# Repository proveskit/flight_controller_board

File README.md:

# flight_controller_board
This is the repo for the main Flight Controller (FC) Board for the PROVES Kit.

For detailed documentation on the Flight Controller Board, check out the docs [here](https://docs.proveskit.space/en/latest/core_documentation/hardware/FC_board/). 

# Quick Start
If you have just received a flight controller board, getting started with developing on one is quick and easy! V4 Flight Controller Boards require the soldering of the JP1 solder jumper to enable powering via USB (it is in the bottom right). V5 Flight Controller Boards have a nifty switch! Once the board is powered up you can refer to [our quick start guide](https://proveskit.github.io/pysquared/getting-started/) for notes on how to get code loaded and the board running.

## Flight Heritage and Version History
| Version | Flights | Status |
| ----------- | ----------- | ----------- |
| V0 | Unflown | Deprecated |
| V1 | Pleiades - Yearling, Pleiades - Squared | Deprecated |
| V2 | Unflown | Deprecated |
| V3 | Unflown | Deprecated |
| V4a (aka V1a Internal) | Unflown | Deprecated |
| V4b | Unflown | Deprecated |
| V4c | Pleiades - Orpheus, InspireFly Content Cube | Dev Only Support |
| V5dev | Unflown | Deprecated |
| V5a | Unflown | Deprecated |
| V5b | Unflown | Deprecated |
| V5c | Unflown | Deprecated |
| V5d | Unflown | Deprecated |
| V5d Pro | Unflown | Supported |
| V5d Pro Rev 1 | PROVES - Alycone, PROVES - Atlas, PROVES - Electra, HUCSat-1 | Supported |
| V5d Pro Rev 2 | Unflown | Supported |
| V5e | Unflown | Dev Support Only |
| V5e Pro Rev 1 | PROVES - Maia, PROVES - Taygeta | Supported |

V0 through V3 Flight Controller Boards were the cornerstone of the 2023 Release V1 PROVES Kit. With the 2024 V2 PROVES Kit we introduced the V4 Flight Controller board and changed the version scheme to have `a`, `b`, `c`, etc varients of a single version rather than ascending the version ladder in record time (we'd be on V17 now if we did that!). This change was primarily based on the idea that a revisions on a major version number would be similar enough to each other to not require completely different firmware to be compiled for operation.

For V5d we added a "Pro" for "Production" version!

## Current Features
The Latest (V5e) FC board implements the following components: 
- RP2350A Microcontroller
- 128M-Bit W25Q128JVSIQ Flash Memory
- HopeRF RFM9X UHF Radio Module Slot
- Ebyte E28-2G4M27S S-Band Radio
- OreSat Derived Radiation Tolerant Watchdog Circuit!
- SD Card Emulating NAND Flash
- TCA9548ARGER(Q1) I2C Multiplexer
- RV3028 Real Time Clock
- LSM6DSOTR Accelerometer and Gyroscope
- LSM303AGRTR Magnetometer
- MCP23017T-E/SS I2C GPIO Expander
- AP22652W6-7 Load Switches
- MCP9808T-E/MS I2C Temperature Sensor
- LT3652IMSE MPP Solar Charge Controller
- INA260 I2C Power Monitor
- TPS54225PWPR 3.3V Switching Voltage Regulator
- TPS54225PWPR 5V Switching Voltage Regulator

## Current Status and Upcoming Plans
The latest V5 generation of Flight Controller boards takes in lessons learned from Orpheus and InspireFly to create a 2025 Release V3 of the PROVES Kit. Both V5dev and V5a will not be distributed beyond the PROVES developer community due to significant design errata that make them tricky to work with. The incoming V5b is intended to be the stable release for this version of the kit.

Lessons learned from V3 PROVES Kit will be directly applied to the creation of a V6 Flight Controller Board generation for V4 PROVES Kit. We plan to continually support the latest and previous PROVES Kit Versions starting with the V3 Release. This means that V2 Kits will continue to receive updates until V4 is officially released.

### The Plan From 2024
Currently we are in production for V1.5 PROVES Kits, which are an interesting middle step between the V1 Kits (which flew on all the Yearling satellites) and V2 (which we are hoping to fly on all the Pleiades Five satellites). One of the main changes between V1 and V2 will be transitioning the flight controller from being mounted to the Z+ face of the satellite to an internal board. This move is intended to improve the thermal performance and radiation tolerance of the avionics stack. 

## Legacy Support
As of May 2025 we are officially no longer supporting any FC boards prior to V4. If you happen to have a PROVES Kit (usually a V1 PROVES Kit manufactured in 2023) that still uses a V1, V2, or V3 Flight Controller board and need support, please open an issue on this GitHub repo and ping @mikefly123 for help! 

### (LEGACY) Internal FC Boards 
1. If you do not plan on connecting a battery board, ensure that the ```JP1``` solder jumper is connected to enable powering the board via USB.
2. Solder on the Radio Module and an antenna or SMA connect as needed.
3. Plug in a USB Cable!
4. If a CircuitPython file system does not appear, you may have to flash the board with firmware. This firmware can be found [here](https://github.com/proveskit/flight_controller_board/tree/main/Firmware)
5. Continue to the [PROVES Quick Start Guide](https://docs.proveskit.space/en/latest/quick_start/proves_quick_start/) for more!
> Note: If you are using USB power for the radio it may not perform as expected due to a lack of 5V power. 

> NOTE: The V1 and V2 boards are not recommended for flight due to a high suspectibility to thermal and radiation effects. These boards are still perfectly fine for ground testing and educational use. Bronco Space is currently conducting testing to flush out these issues and will be mitigating these potential issues in V3. If you would like to receive eval hardware of the new version please contact Michael Pham: mlpham@cpp.edu

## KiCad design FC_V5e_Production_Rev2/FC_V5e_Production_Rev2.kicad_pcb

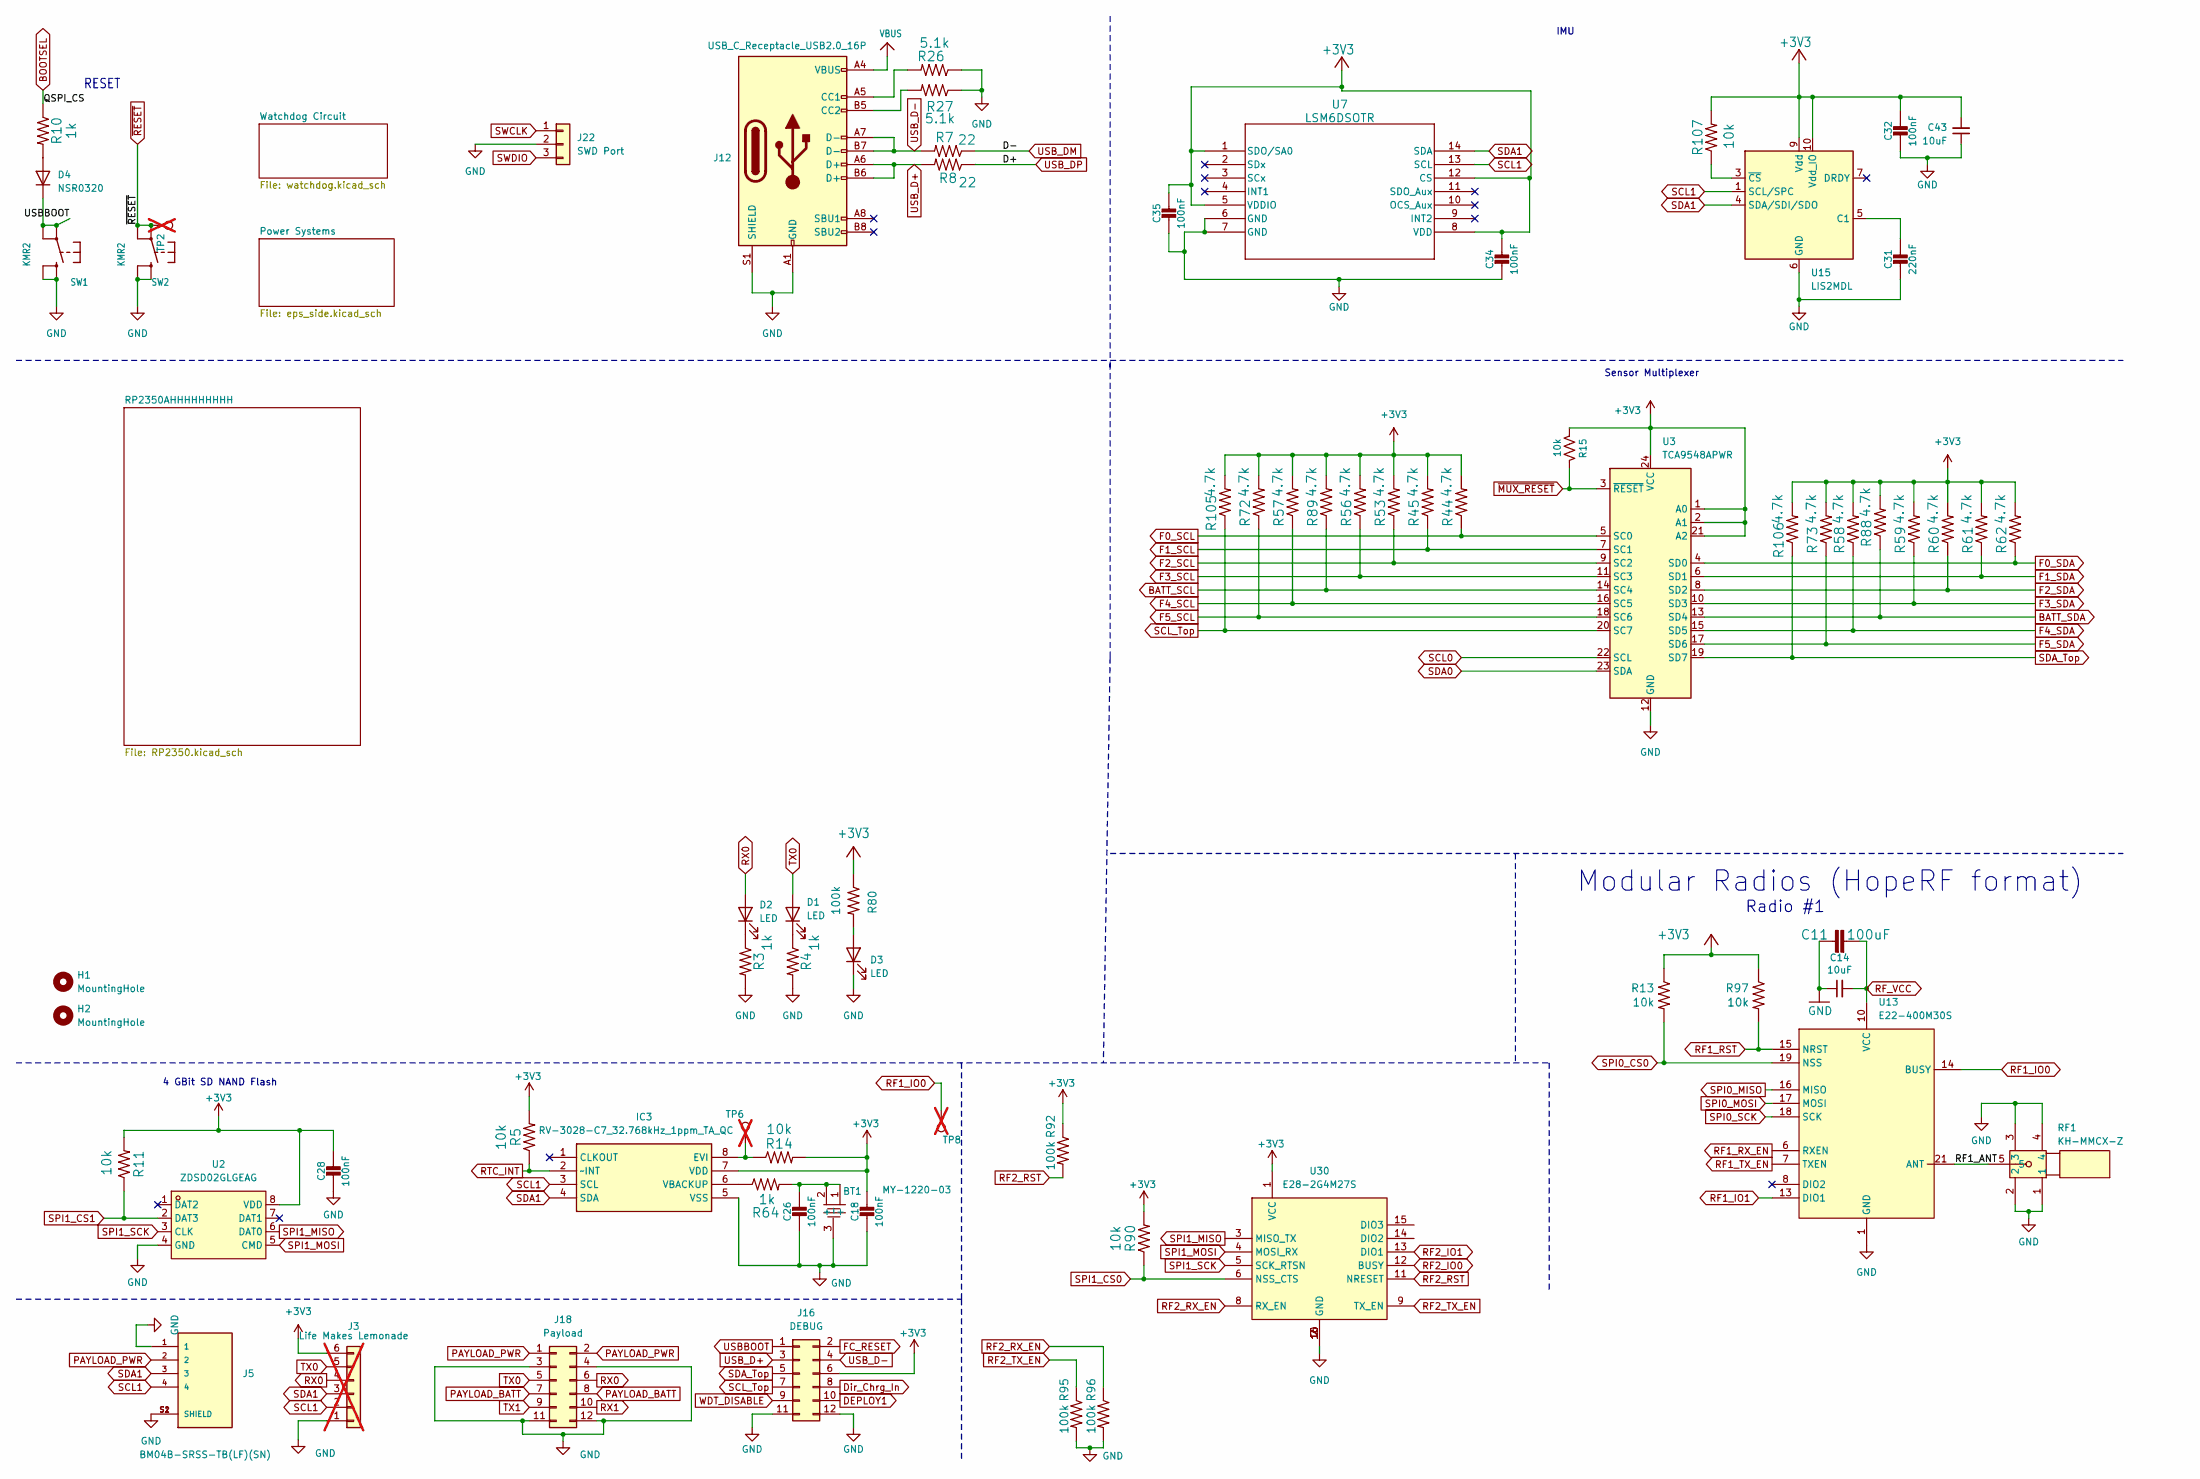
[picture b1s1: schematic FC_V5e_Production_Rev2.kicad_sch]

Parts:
BT1: MY-1220-03; BAT-SMD_MY-1220-03; LCSC Part C964818
C11: 100uF; C_1210_3225Metric
C14: 10uF; C_0603_1608Metric
C18, C26, C28, C32, C34, C35: 100nF; C_0402_1005Metric
C31: 220nF; C_0402_1005Metric
C43: 10uF; C_0603_1608Metric; MPN GRT188R61C106KE13D
D1, D2, D3: LED; LED_0603_1608Metric
D4: NSR0320; D_SOD-323F
H1, H2: MountingHole
IC3: RV-3028-C7_32.768kHz_1ppm_TA_QC; RV3028C7; Mouser Part Number 428-203591-MG01
J3: Life Makes Lemonade; PinHeader_1x06_P2.54mm_Vertical; not fitted
J5: BM04B-SRSS-TB(LF)(SN); JST_BM04B-SRSS-TB(LF)(SN); MPN BM04B-SRSS-TB(LF)(SN)
J12: USB_C_Receptacle_USB2.0_16P; USB_C_Receptacle_HRO_TYPE-C-31-M-12; MPN TYPE-C-31-M-12
J16: DEBUG; Hirose_DF11-12DP-2DSA_2x06_P2.00mm_Vertical; MPN DF11-12DP-2DSA(08)
J18: Payload; Hirose_DF11-12DP-2DSA_2x06_P2.00mm_Vertical; MPN DF11-12DP-2DSA(08)
J22: SWD Port; JST_SH_BM03B-SRSS-TB_1x03-1MP_P1.00mm_Vertical; MPN BM03B-SRSS-TB(LF)(SN)
R3, R4, R10, R64: 1k; R_0603_1608Metric
R5, R11, R13, R14, R15, R90, R97, R107: 10k; R_0603_1608Metric
R7, R8: 22; R_0402_1005Metric
R26, R27: 5.1k; R_0603_1608Metric
R44, R45, R53, R56, R57, R58, R59, R60, R61, R62, R72, R73, R88, R89, R105, R106: 4.7k; R_0402_1005Metric
R80, R92, R95, R96: 100k; R_0603_1608Metric
RF1: KH-MMCX-Z; MMCX-TH_KH-MMCX-Z; LCSC Part C530664
SW1, SW2: KMR2; BTN_KMR2_4.6X2.8
TP2, TP6, TP8: RESET; TestPoint_Loop_D1.80mm_Drill1.0mm_Beaded; not fitted
U2: ZDSD02GLGEAG; LGA-8_L8.0-W6.0-P1.27-TL-1; LCSC Part C2875853
U3: TCA9548APWR; TSSOP-24_4.4x7.8mm_P0.65mm
U7: LSM6DSOTR; LGA-14_3x2.5mm_P0.5mm_LayoutBorder3x4y
U13: E22-400M30S; WIRELM-SMD_E22-400M30S; LCSC Part C411292
U15: LIS2MDL; LGA-12_2x2mm_P0.5mm
U30: E28-2G4M27S; WIRELM-SMD_E28-2G4M2XS; LCSC Part C411312

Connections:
+3V3: C18.1, C28.1, C32.1, C34.1, C35.1, C43.2, IC3.7 (VDD), J3.6, J16.6, R5.2, R11.2, R13.1, R14.2, R15.1, R44.2, R45.2, R53.2, R56.2, R57.2, R58.2, R59.2, R60.2, R61.2, R62.2, R72.2, R73.2, R80.1, R88.2, R89.2, R90.2, R92.1, R97.1, R105.2, R106.2, R107.2, U2.8 (VDD), U3.1 (A0), U3.2 (A1), U3.21 (A2), U3.24 (VCC), U7.1 (SDO/SA0), U7.5 (VDDIO), U7.8 (VDD), U7.12 (CS), U15.9 (Vdd), U15.10 (Vdd_IO), U30.1 (VCC); also elsewhere on the board
/RF1_ANT: RF1.5, U13.21 (ANT)
BATT_SCL: R89.1, U3.14 (SC4); also elsewhere on the board
BATT_SDA: R88.1, U3.13 (SD4); also elsewhere on the board
BOOTSEL: R10.1; also elsewhere on the board
DEPLOY1: J16.10; also elsewhere on the board
Dir_Chrg_In: J16.8; also elsewhere on the board
F0_SCL: R44.1, U3.5 (SC0); also elsewhere on the board
F0_SDA: R62.1, U3.4 (SD0); also elsewhere on the board
F1_SCL: R45.1, U3.7 (SC1); also elsewhere on the board
F1_SDA: R61.1, U3.6 (SD1); also elsewhere on the board
F2_SCL: R53.1, U3.9 (SC2); also elsewhere on the board
F2_SDA: R60.1, U3.8 (SD2); also elsewhere on the board
F3_SCL: R56.1, U3.11 (SC3); also elsewhere on the board
F3_SDA: R59.1, U3.10 (SD3); also elsewhere on the board
F4_SCL: R57.1, U3.16 (SC5); also elsewhere on the board
F4_SDA: R58.1, U3.15 (SD5); also elsewhere on the board
F5_SCL: R72.1, U3.18 (SC6); also elsewhere on the board
F5_SDA: R73.1, U3.17 (SD6); also elsewhere on the board
FC_RESET: J16.2, SW2.A, SW2.A' (P1), TP2.1 (1_1); also elsewhere on the board
GND: BT1.3 (-), C11.1, C14.1, C18.2, C26.2, C28.2, C31.2, C32.2, C34.2, C35.2, C43.1, D3.1 (K), IC3.5 (VSS), J3.1, J5.1, J5.S1 (SHIELD), J5.S2 (SHIELD), J12.A1 (GND), J12.A12 (GND), J12.B1 (GND), J12.B12 (GND), J12.S1 (SHIELD), J16.11, J16.12, J18.3, J18.4, J18.11, J18.12, J22.2, R3.2, R4.2, R26.1, R27.1, R95.2, R96.2, RF1.1, RF1.2, RF1.3, RF1.4, SW1.B (S), SW1.B' (S1), SW2.B (S), SW2.B' (S1), U2.4 (GND), U3.12 (GND), U7.6 (GND), U7.7 (GND), U13.1 (GND), U13.2 (GND), U13.3 (GND), U13.4 (GND), U13.5 (GND), U13.11 (GND), U13.12 (GND), U13.20 (GND), U13.22 (GND), U15.6 (GND), U15.8 (GND), U30.2 (GND), U30.7 (GND), U30.10 (GND), U30.16 (GND); also elsewhere on the board
unnamed: BT1.1 (+), BT1.2 (+), C26.1, R64.2
unnamed: D1.1 (K), R4.1
unnamed: D2.1 (K), R3.1
unnamed: D3.2 (A), R80.2
unnamed: D4.2 (A), R10.2
unnamed: IC3.8 (EVI), R14.1, TP6.1 (1_1)
unnamed: IC3.6 (VBACKUP), R64.1
unnamed: J12.A5 (CC1), R26.2
unnamed: J12.B5 (CC2), R27.2
unnamed: C31.1, U15.5 (C1)
unnamed: R107.1, U15.3 (~CS)
PAYLOAD_BATT: J18.7, J18.8; also elsewhere on the board
PAYLOAD_PWR: J5.2, J18.1, J18.2; also elsewhere on the board
RF1_IO0: TP8.1 (1_1), U13.14 (BUSY); also elsewhere on the board
RF1_IO1: U13.13 (DIO1); also elsewhere on the board
RF1_RST: R97.2, U13.15 (NRST); also elsewhere on the board
RF1_RX_EN: U13.6 (RXEN); also elsewhere on the board
RF1_TX_EN: U13.7 (TXEN); also elsewhere on the board
RF2_IO0: U30.12 (BUSY); also elsewhere on the board
RF2_IO1: U30.13 (DIO1); also elsewhere on the board
RF2_RST: R92.2, U30.11 (NRESET); also elsewhere on the board
RF2_RX_EN: R96.1, U30.8 (RX_EN); also elsewhere on the board
RF2_TX_EN: R95.1, U30.9 (TX_EN); also elsewhere on the board
RF_VCC: C11.2, C14.2, U13.9 (VCC), U13.10 (VCC); also elsewhere on the board
RTC_INT: IC3.2 (~INT), R5.1; also elsewhere on the board
RX0: D2.2 (A), J3.4, J18.6; also elsewhere on the board
RX1: J18.10; also elsewhere on the board
SCL0: U3.22 (SCL); also elsewhere on the board
SCL1: IC3.3 (SCL), J3.2, J5.4, U7.13 (SCL), U15.1 (SCL/SPC); also elsewhere on the board
SCL_Top: J16.7, R105.1, U3.20 (SC7)
SDA0: U3.23 (SDA); also elsewhere on the board
SDA1: IC3.4 (SDA), J3.3, J5.3, U7.14 (SDA), U15.4 (SDA/SDI/SDO); also elsewhere on the board
SDA_Top: J16.5, R106.1, U3.19 (SD7)
SPI0_CS0: R13.2, U13.19 (NSS); also elsewhere on the board
SPI0_MISO: U13.16 (MISO); also elsewhere on the board
SPI0_MOSI: U13.17 (MOSI); also elsewhere on the board
SPI0_SCK: U13.18 (SCK); also elsewhere on the board
SPI1_CS0: R90.1, U30.6 (NSS_CTS); also elsewhere on the board
SPI1_CS1: R11.1, U2.2 (DAT3); also elsewhere on the board
SPI1_MISO: U2.6 (DAT0), U30.3 (MISO_TX); also elsewhere on the board
SPI1_MOSI: U2.5 (CMD), U30.4 (MOSI_RX); also elsewhere on the board
SPI1_SCK: U2.3 (CLK), U30.5 (SCK_RTSN); also elsewhere on the board
SWCLK: J22.1; also elsewhere on the board
SWDIO: J22.3; also elsewhere on the board
TX0: D1.2 (A), J3.5, J18.5; also elsewhere on the board
TX1: J18.9; also elsewhere on the board
USBBOOT: D4.1 (K), J16.1, SW1.A, SW1.A' (P1)
USB_D+: J12.A6 (D+), J12.B6 (D+), J16.3, R8.2
USB_D-: J12.A7 (D-), J12.B7 (D-), J16.4, R7.2
USB_DM: R7.1; also elsewhere on the board
USB_DP: R8.1; also elsewhere on the board
VBUS: J12.A4 (VBUS), J12.A9 (VBUS), J12.B4 (VBUS), J12.B9 (VBUS); also elsewhere on the board
WDT_DISABLE: J16.9; also elsewhere on the board
~MUX_RESET: R15.2, U3.3 (~RESET); also elsewhere on the board

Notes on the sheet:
4 GBit SD NAND Flash
Radio #1
Modular Radios (HopeRF format)
Sensor Multiplexer
RESET
IMU

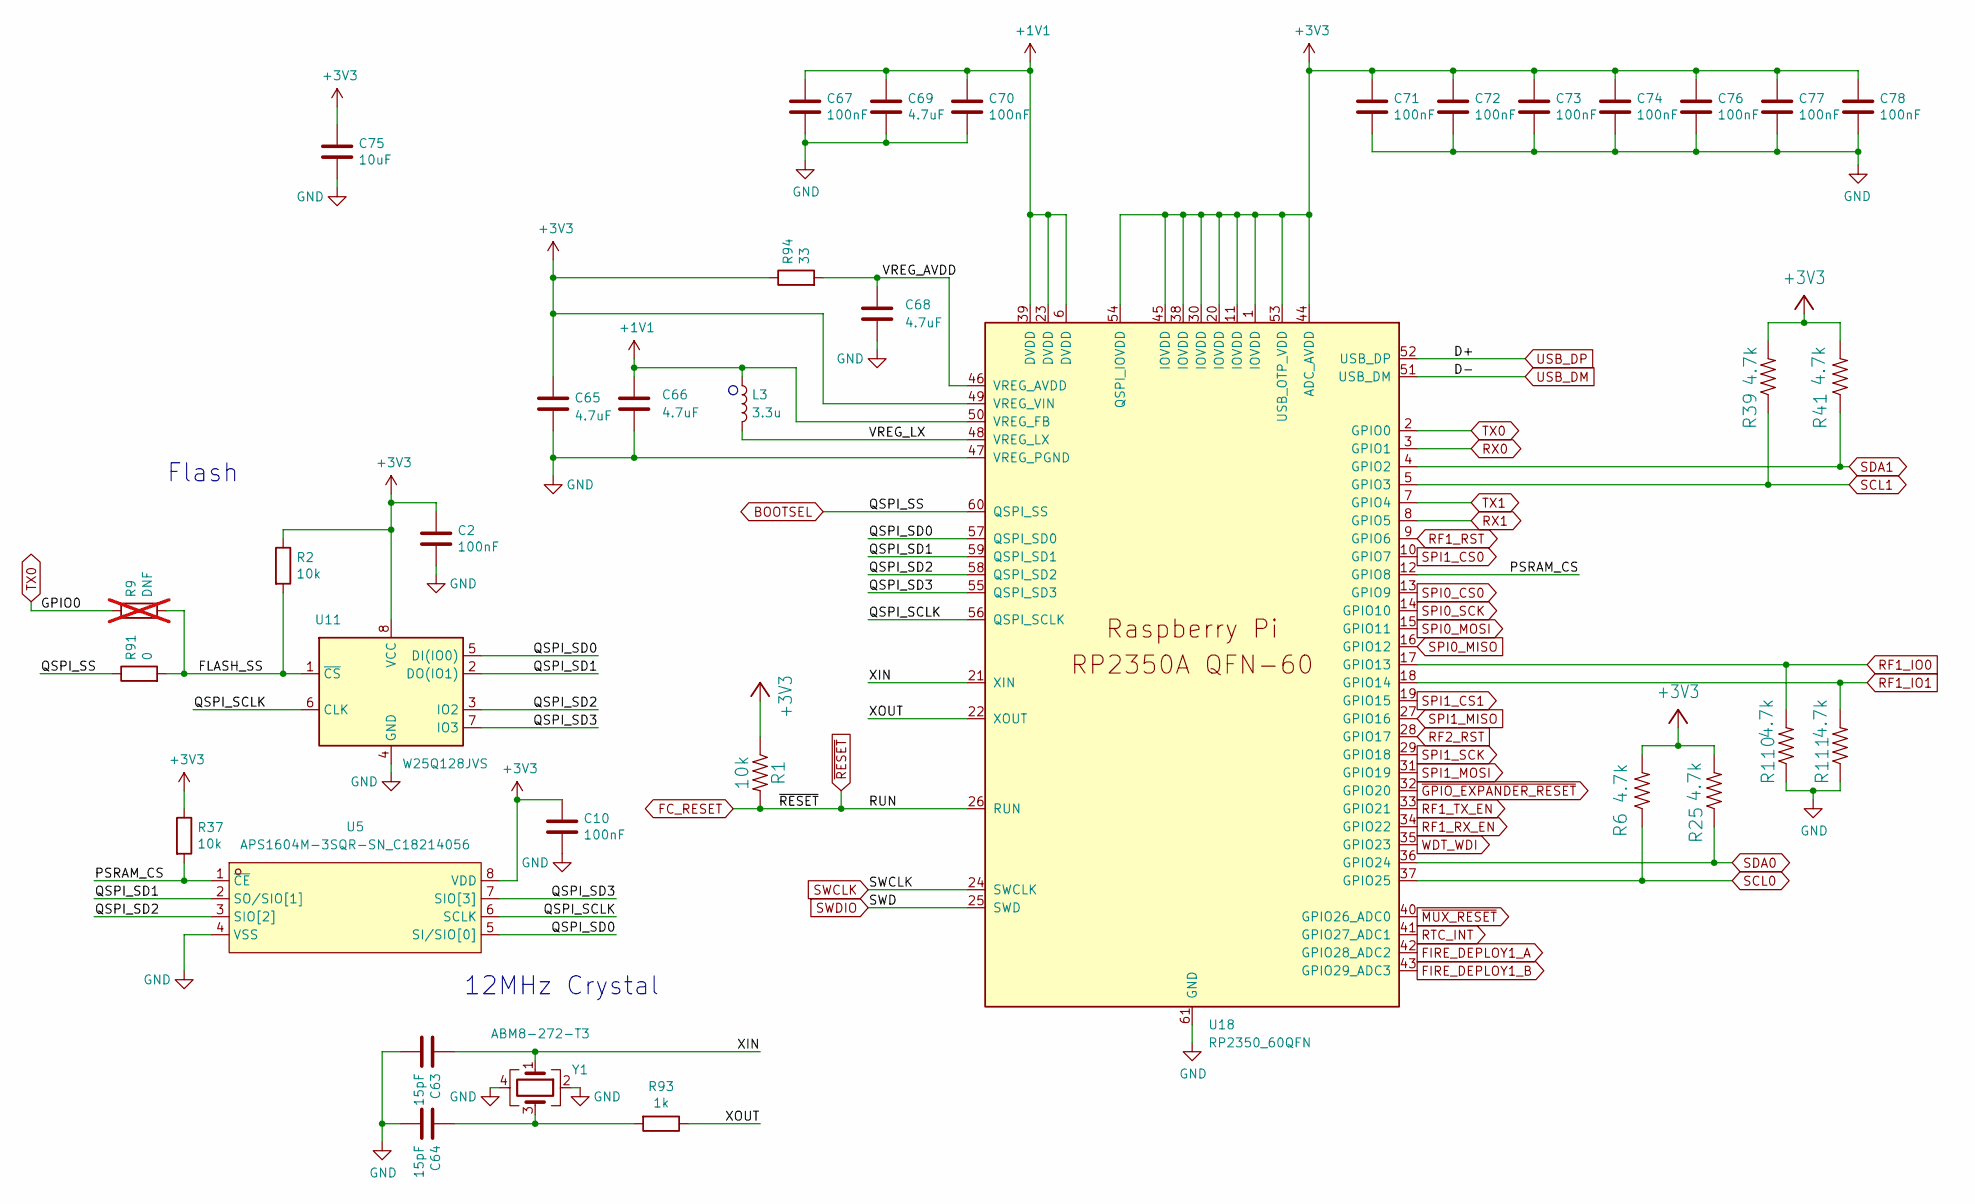
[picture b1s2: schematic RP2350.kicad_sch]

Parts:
C2, C10, C67, C70, C71, C72, C73, C74, C76, C77, C78: 100nF; C_0402_1005Metric
C63, C64: 15pF; C_0402_1005Metric
C65, C66: 4.7uF; C_0402_1005Metric_small_pads
C68, C69: 4.7uF; C_0402_1005Metric
C75: 10uF; C_0805_2012Metric
L3: 3.3u; L_pol_2016
R1: 10k; R_0603_1608Metric
R2, R37: 10k; R_0402_1005Metric
R6, R25, R39, R41, R110, R111: 4.7k; R_0402_1005Metric
R9: DNF; R_0402_1005Metric; not fitted
R91: 0; R_0402_1005Metric
R93: 1k; R_0402_1005Metric
R94: 33; R_0402_1005Metric
U5: APS1604M-3SQR-SN_C18214056; SOIC-8_L4.9-W3.9-P1.27-LS6.0-BL; LCSC Part C18214056
U11: W25Q128JVS; SOIC-8_5.3x5.3mm_P1.27mm
U18: RP2350_60QFN; RP2350-QFN-60-1EP_7x7_P0.4mm_EP3.4x3.4mm_ThermalVias
Y1: ABM8-272-T3; Crystal_SMD_3225-4Pin_3.2x2.5mm

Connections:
+1V1: C66.1, C67.1, C69.1, C70.1, L3.1, U18.6 (DVDD), U18.23 (DVDD), U18.39 (DVDD), U18.50 (VREG_FB)
+3V3: C2.1, C10.1, C65.1, C71.1, C72.1, C73.1, C74.1, C75.1, C76.1, C77.1, C78.1, R1.1, R2.1, R6.2, R25.2, R37.1, R39.2, R41.2, R94.1, U5.8 (VDD), U11.8 (VCC), U18.1 (IOVDD), U18.11 (IOVDD), U18.20 (IOVDD), U18.30 (IOVDD), U18.38 (IOVDD), U18.44 (ADC_AVDD), U18.45 (IOVDD), U18.49 (VREG_VIN), U18.53 (USB_OTP_VDD), U18.54 (QSPI_IOVDD); also elsewhere on the board
/RP2350AHHHHHHHHH/FLASH_SS: R2.2, R9.2, R91.2, U11.1 (~CS)
/RP2350AHHHHHHHHH/PSRAM_CS: R37.2, U5.1 (~CE), U18.12 (GPIO8)
/RP2350AHHHHHHHHH/QSPI_SCLK: U5.6 (SCLK), U11.6 (CLK), U18.56 (QSPI_SCLK)
/RP2350AHHHHHHHHH/QSPI_SD0: U5.5 (SI/SIO[0]), U11.5 (DI(IO0)), U18.57 (QSPI_SD0)
/RP2350AHHHHHHHHH/QSPI_SD1: U5.2 (SO/SIO[1]), U11.2 (DO(IO1)), U18.59 (QSPI_SD1)
/RP2350AHHHHHHHHH/QSPI_SD2: U5.3 (SIO[2]), U11.3 (IO2), U18.58 (QSPI_SD2)
/RP2350AHHHHHHHHH/QSPI_SD3: U5.7 (SIO[3]), U11.7 (IO3), U18.55 (QSPI_SD3)
/RP2350AHHHHHHHHH/VREG_AVDD: C68.1, R94.2, U18.46 (VREG_AVDD)
/RP2350AHHHHHHHHH/VREG_LX: L3.2, U18.48 (VREG_LX)
/RP2350AHHHHHHHHH/XIN: C63.1, U18.21 (XIN), Y1.1
/RP2350AHHHHHHHHH/XOUT: R93.1, U18.22 (XOUT)
BOOTSEL: R91.1, U18.60 (QSPI_SS); also elsewhere on the board
FC_RESET: R1.2, U18.26 (RUN); also elsewhere on the board
FIRE_DEPLOY1_A: U18.42 (GPIO28_ADC2); also elsewhere on the board
FIRE_DEPLOY1_B: U18.43 (GPIO29_ADC3); also elsewhere on the board
GND: C2.2, C10.2, C63.2, C64.2, C65.2, C66.2, C67.2, C68.2, C69.2, C70.2, C71.2, C72.2, C73.2, C74.2, C75.2, C76.2, C77.2, C78.2, R110.1, R111.1, U5.4 (VSS), U11.4 (GND), U18.47 (VREG_PGND), U18.61 (GND), Y1.2, Y1.4; also elsewhere on the board
unnamed: C64.1, R93.2, Y1.3
RF1_IO0: R110.2, U18.17 (GPIO13); also elsewhere on the board
RF1_IO1: R111.2, U18.18 (GPIO14); also elsewhere on the board
RF1_RST: U18.9 (GPIO6); also elsewhere on the board
RF1_RX_EN: U18.34 (GPIO22); also elsewhere on the board
RF1_TX_EN: U18.33 (GPIO21); also elsewhere on the board
RF2_RST: U18.28 (GPIO17); also elsewhere on the board
RTC_INT: U18.41 (GPIO27_ADC1); also elsewhere on the board
RX0: U18.3 (GPIO1); also elsewhere on the board
RX1: U18.8 (GPIO5); also elsewhere on the board
SCL0: R6.1, U18.37 (GPIO25); also elsewhere on the board
SCL1: R39.1, U18.5 (GPIO3); also elsewhere on the board
SDA0: R25.1, U18.36 (GPIO24); also elsewhere on the board
SDA1: R41.1, U18.4 (GPIO2); also elsewhere on the board
SPI0_CS0: U18.13 (GPIO9); also elsewhere on the board
SPI0_MISO: U18.16 (GPIO12); also elsewhere on the board
SPI0_MOSI: U18.15 (GPIO11); also elsewhere on the board
SPI0_SCK: U18.14 (GPIO10); also elsewhere on the board
SPI1_CS0: U18.10 (GPIO7); also elsewhere on the board
SPI1_CS1: U18.19 (GPIO15); also elsewhere on the board
SPI1_MISO: U18.27 (GPIO16); also elsewhere on the board
SPI1_MOSI: U18.31 (GPIO19); also elsewhere on the board
SPI1_SCK: U18.29 (GPIO18); also elsewhere on the board
SWCLK: U18.24 (SWCLK); also elsewhere on the board
SWDIO: U18.25 (SWD); also elsewhere on the board
TX0: R9.1, U18.2 (GPIO0); also elsewhere on the board
TX1: U18.7 (GPIO4); also elsewhere on the board
USB_DM: U18.51 (USB_DM); also elsewhere on the board
USB_DP: U18.52 (USB_DP); also elsewhere on the board
WDT_WDI: U18.35 (GPIO23); also elsewhere on the board
~GPIO_EXPANDER_RESET: U18.32 (GPIO20); also elsewhere on the board
~MUX_RESET: U18.40 (GPIO26_ADC0); also elsewhere on the board

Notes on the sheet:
12MHz Crystal
Flash

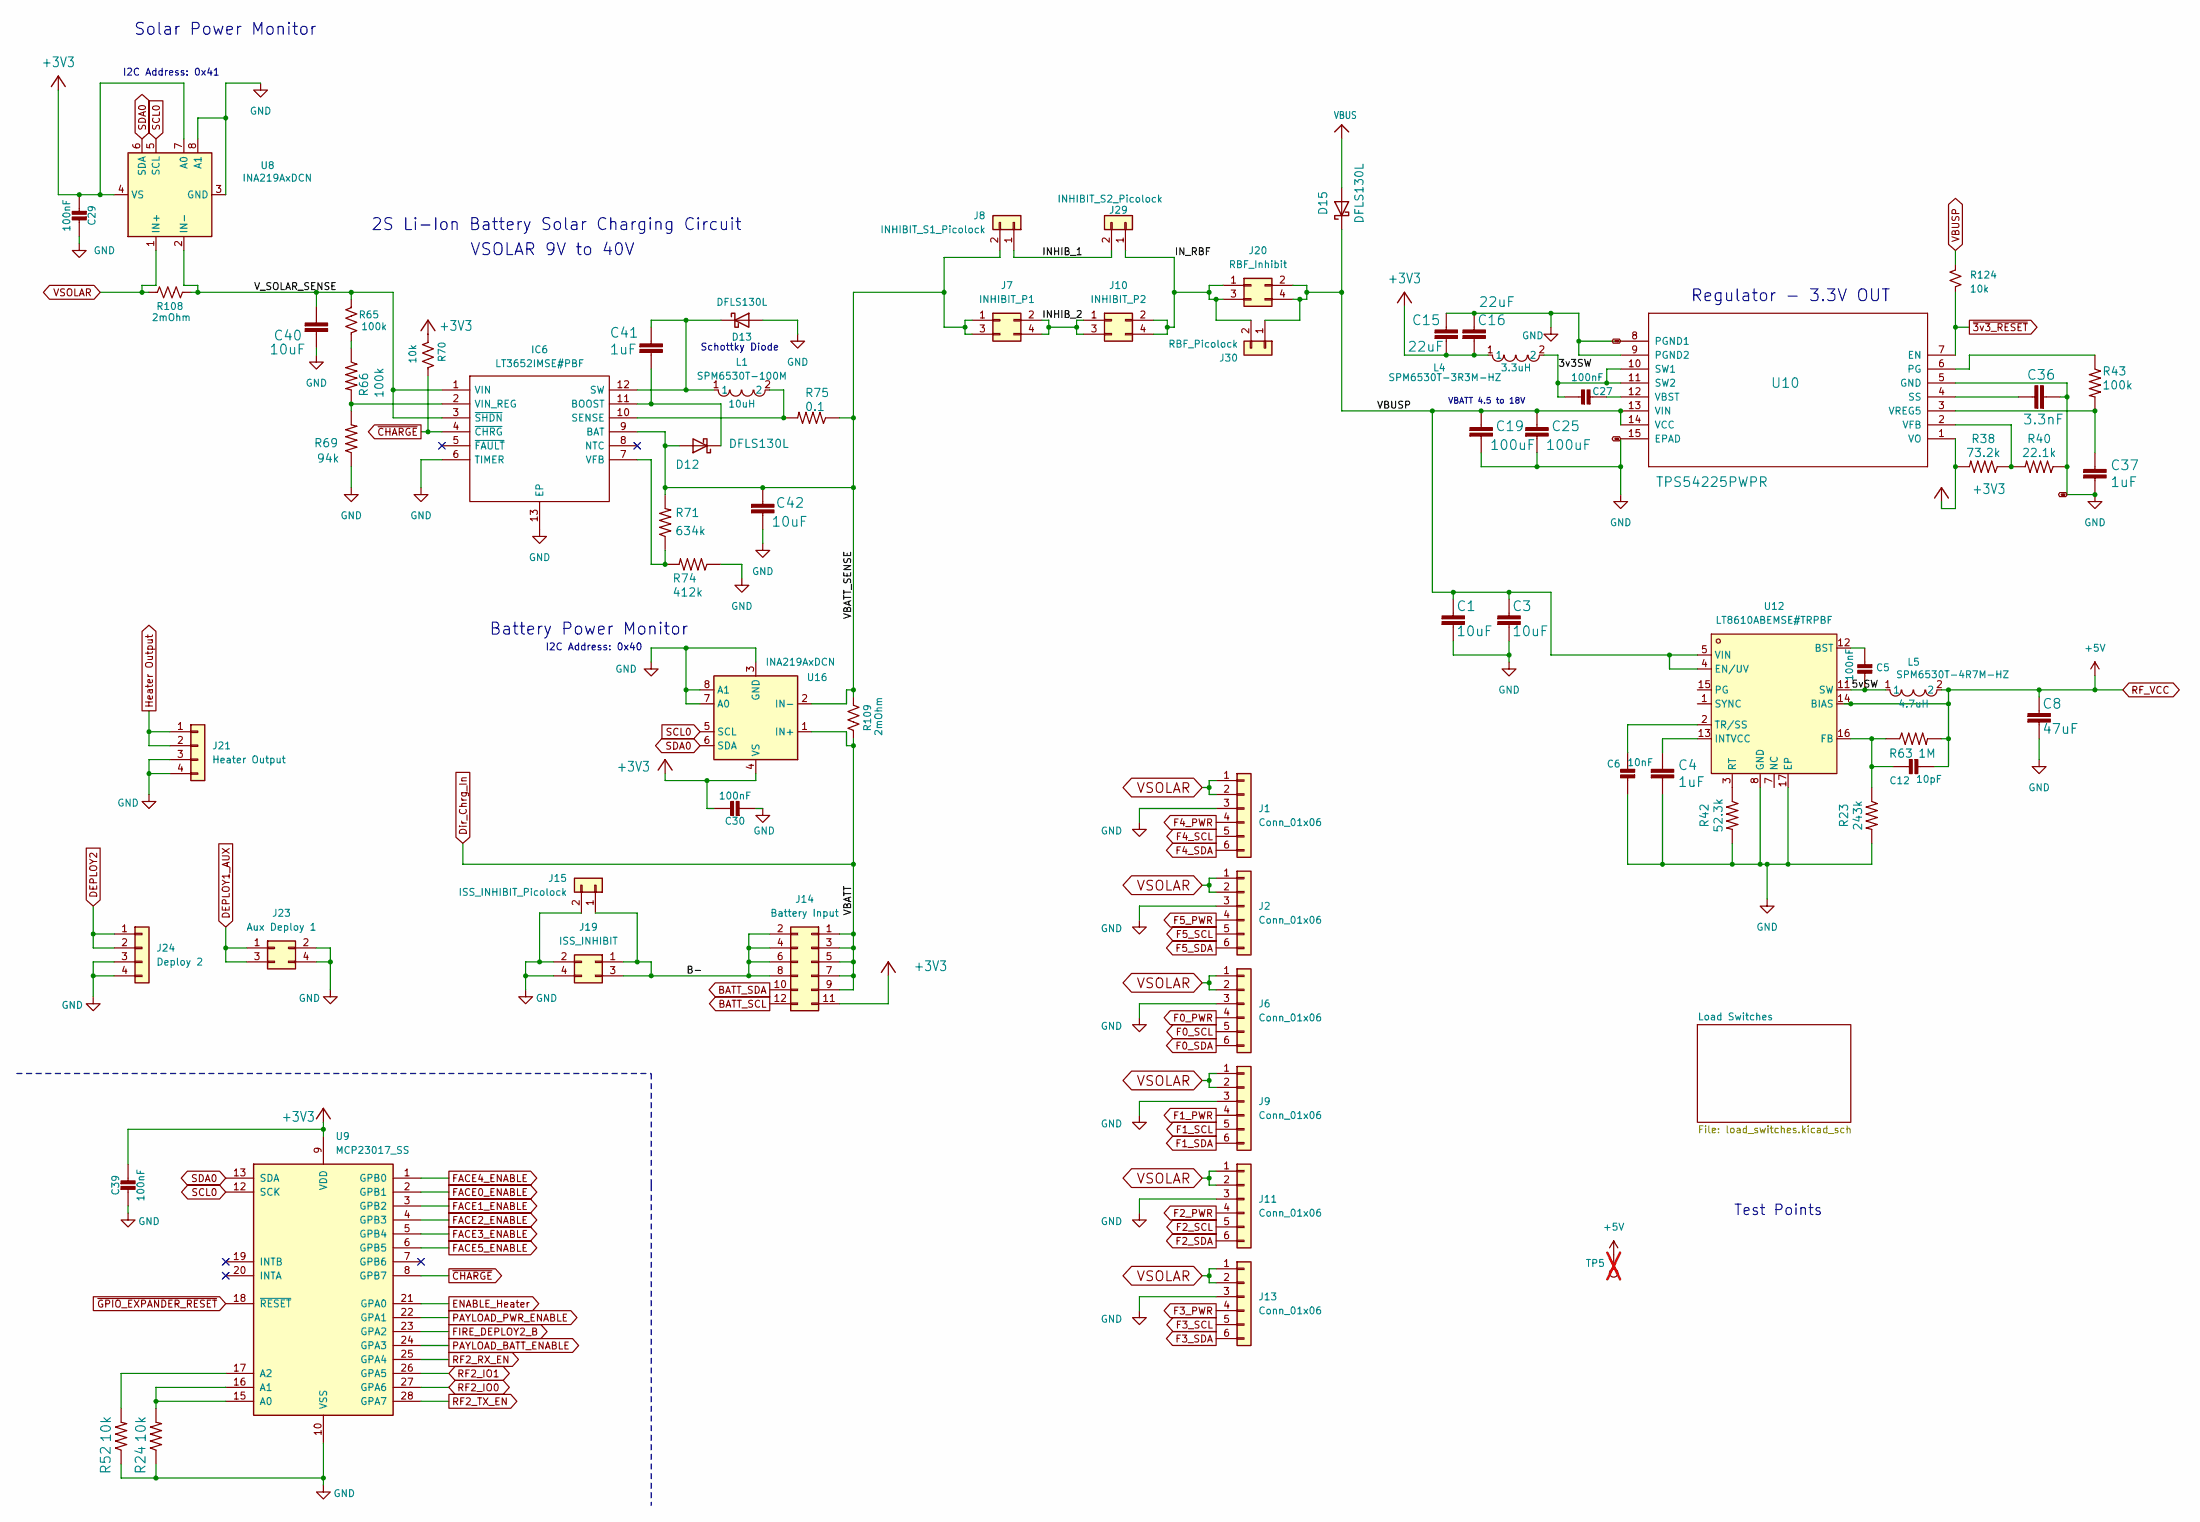
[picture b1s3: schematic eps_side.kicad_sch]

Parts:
C1, C3, C40, C42: 10uF; C_0603_1608Metric
C4, C37, C41: 1uF; C_0603_1608Metric
C5, C27, C29, C30, C39: 100nF; C_0402_1005Metric
C6: 10nF; C_0402_1005Metric
C8: 47uF; C_1210_3225Metric
C12: 10pF; C_0402_1005Metric
C15, C16: 22uF; C_0603_1608Metric
C19, C25: 100uF; C_1210_3225Metric
C36: 3.3nF; C_0603_1608Metric
D12, D15: DFLS130L; D_PowerDI-123; Manufacturer_Part_Number DFLS130L-7
D13: DFLS130L; D_PowerDI-123
IC6: LT3652IMSE#PBF; MSOP-12-1EP_3x4mm_P0.65mm_EP1.65x2.85mm; Mouser Part Number 584-LT3652IMSE#PBF
J1, J2, J6, J9, J11, J13: Conn_01x06; Molex_Pico-Lock_504050-0691_1x06-1MP_P1.50mm_Horizontal; MPN 5040500691
J7: INHIBIT_P1; Hirose_DF11-4DP-2DSA_2x02_P2.00mm_Vertical; MPN DF11-4DP-2DSA(08)
J8: INHIBIT_S1_Picolock; Molex_Pico-Lock_504050-0291_1x02-1MP_P1.50mm_Horizontal; MPN 5040500291
J10: INHIBIT_P2; Hirose_DF11-4DP-2DSA_2x02_P2.00mm_Vertical; MPN DF11-4DP-2DSA(08)
J14: Battery Input; Hirose_DF11-12DP-2DSA_2x06_P2.00mm_Vertical; MPN DF11-12DP-2DSA(08)
J15: ISS_INHIBIT_Picolock; Molex_Pico-Lock_504050-0291_1x02-1MP_P1.50mm_Horizontal; MPN 5040500291
J19: ISS_INHIBIT; Hirose_DF11-4DP-2DSA_2x02_P2.00mm_Vertical; MPN DF11-4DP-2DSA(08)
J20: RBF_Inhibit; Hirose_DF11-4DP-2DSA_2x02_P2.00mm_Vertical; MPN DF11-4DP-2DSA(08)
J21: Heater Output; Molex_Pico-Lock_504050-0491_1x04-1MP_P1.50mm_Horizontal; MPN 5040500491
J23: Aux Deploy 1; CONN-SMD_4P-P2.00_DF11CZ-4DP-2V-27; MPN DF11CZ-4DP-2V(27)
J24: Deploy 2; Molex_Pico-Lock_504050-0491_1x04-1MP_P1.50mm_Horizontal; MPN 5040500491
J29: INHIBIT_S2_Picolock; Molex_Pico-Lock_504050-0291_1x02-1MP_P1.50mm_Horizontal; MPN 5040500291
J30: RBF_Picolock; Molex_Pico-Lock_504050-0291_1x02-1MP_P1.50mm_Horizontal; MPN 5040500291
L1: SPM6530T-100M; IND-SMD_L7.1-W6.5-P5.60; LCSC Part C112288
L4: SPM6530T-3R3M-HZ; IND-SMD_L7.1-W6.5; LCSC Part C404816
L5: SPM6530T-4R7M-HZ; IND-SMD_L7.1-W6.5-P5.60; LCSC Part C360729
R23: 243k; R_0603_1608Metric
R24, R52, R70: 10k; R_0603_1608Metric
R38: 73.2k; R_0603_1608Metric
R40: 22.1k; R_0603_1608Metric
R42: 52.3k; R_0603_1608Metric
R43, R65, R66: 100k; R_0603_1608Metric
R63: 1M; R_0603_1608Metric
R69: 94k; R_0603_1608Metric
R71: 634k; R_0603_1608Metric
R74: 412k; R_0603_1608Metric
R75: 0.1; R_2512_6332Metric
R108, R109: 2mOhm; LED_1210_3225Metric
R124: 10k; R_0603_1608Metric; MPN RMCF0603FT10K0
TP5: TestPoint; TestPoint_Loop_D1.80mm_Drill1.0mm_Beaded; not fitted
U8, U16: INA219AxDCN; SOT-23-8
U9: MCP23017_SS; SSOP-28_5.3x10.2mm_P0.65mm
U10: TPS54225PWPR; PWP14_2P31X2P46-L; Manufacturer_Part_Number TPS54225PWPR
U12: LT8610ABEMSE#TRPBF; MSOP-16_L4.0-W3.0-P0.50-LS4.9-BL-EP; LCSC Part C580306

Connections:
+3V3: C15.2, C16.2, C29.2, C30.1, C39.1, J14.11, L4.1, R38.2, R70.1, U8.4 (VS), U8.7 (A0), U9.9 (VDD), U10.1 (VO), U16.4 (VS); also elsewhere on the board
/Power Systems/3v3SW: C27.1, L4.2, U10.10 (SW1), U10.11 (SW2)
/Power Systems/5vSW: C5.1, L5.1, U12.9 (SW), U12.10 (SW), U12.11 (SW)
/Power Systems/B-: J14.2, J14.4, J14.6, J14.8, J15.1, J19.1, J19.3
/Power Systems/INHIB_1: J8.1, J29.2
/Power Systems/INHIB_2: J7.2, J7.4, J10.1, J10.3
/Power Systems/IN_RBF: J10.2, J10.4, J20.1, J20.3, J29.1, J30.2
/Power Systems/VBATT_SENSE: C42.1, D12.2 (A), IC6.9 (BAT), J7.1, J7.3, J8.2, R71.2, R75.1, R109.2, U16.2 (IN-)
/Power Systems/V_SOLAR_SENSE: C40.1, IC6.1 (VIN), IC6.3 (~SHDN), R65.1, R108.2, U8.2 (IN-)
BATT_SCL: J14.12; also elsewhere on the board
BATT_SDA: J14.10; also elsewhere on the board
DEPLOY1_AUX: J23.1, J23.3; also elsewhere on the board
DEPLOY2: J24.1, J24.2; also elsewhere on the board
Dir_Chrg_In: J14.1, J14.3, J14.5, J14.7, J14.9, R109.1, U16.1 (IN+); also elsewhere on the board
ENABLE_Heater: U9.21 (GPA0); also elsewhere on the board
F0_PWR: J6.4; also elsewhere on the board
F0_SCL: J6.5; also elsewhere on the board
F0_SDA: J6.6; also elsewhere on the board
F1_PWR: J9.4; also elsewhere on the board
F1_SCL: J9.5; also elsewhere on the board
F1_SDA: J9.6; also elsewhere on the board
F2_PWR: J11.4; also elsewhere on the board
F2_SCL: J11.5; also elsewhere on the board
F2_SDA: J11.6; also elsewhere on the board
F3_PWR: J13.4; also elsewhere on the board
F3_SCL: J13.5; also elsewhere on the board
F3_SDA: J13.6; also elsewhere on the board
F4_PWR: J1.4; also elsewhere on the board
F4_SCL: J1.5; also elsewhere on the board
F4_SDA: J1.6; also elsewhere on the board
F5_PWR: J2.4; also elsewhere on the board
F5_SCL: J2.5; also elsewhere on the board
F5_SDA: J2.6; also elsewhere on the board
FACE0_ENABLE: U9.2 (GPB1); also elsewhere on the board
FACE1_ENABLE: U9.3 (GPB2); also elsewhere on the board
FACE2_ENABLE: U9.4 (GPB3); also elsewhere on the board
FACE3_ENABLE: U9.5 (GPB4); also elsewhere on the board
FACE4_ENABLE: U9.1 (GPB0); also elsewhere on the board
FACE5_ENABLE: U9.6 (GPB5); also elsewhere on the board
FIRE_DEPLOY2_B: U9.23 (GPA2); also elsewhere on the board
GND: C1.2, C3.2, C4.2, C6.1, C8.2, C15.1, C16.1, C19.2, C25.2, C29.1, C30.2, C36.2, C37.2, C39.2, C40.2, C42.2, D13.2 (A), IC6.6 (TIMER), IC6.13 (EP), J1.3, J2.3, J6.3, J9.3, J11.3, J13.3, J15.2, J19.2, J19.4, J21.3, J21.4, J23.2, J23.4, J24.3, J24.4, R23.2, R24.1, R40.1, R42.2, R52.1, R69.1, R74.1, U8.3 (GND), U8.8 (A1), U9.10 (VSS), U10.5 (GND), U10.8 (PGND1), U10.9 (PGND2), U10.15 (EPAD), U12.8 (GND), U12.17 (EP), U16.3 (GND), U16.7 (A0), U16.8 (A1); also elsewhere on the board
Heater Output: J21.1, J21.2; also elsewhere on the board
unnamed: C41.2, D12.1 (K), IC6.11 (BOOST)
unnamed: C41.1, D13.1 (K), IC6.12 (SW), L1.1
unnamed: IC6.10 (SENSE), L1.2, R75.2
unnamed: IC6.7 (VFB), R71.1, R74.2
unnamed: IC6.2 (VIN_REG), R66.2, R69.2
unnamed: R65.2, R66.1
unnamed: R24.2, U9.15 (A0), U9.16 (A1)
unnamed: R52.2, U9.17 (A2)
unnamed: R43.1, U10.6 (PG)
unnamed: C36.1, U10.4 (SS)
unnamed: C27.2, U10.12 (VBST)
unnamed: R38.1, R40.2, U10.2 (VFB)
unnamed: C37.1, R43.2, U10.3 (VREG5)
unnamed: C5.2, U12.12 (BST)
unnamed: C12.2, R23.1, R63.1, U12.16 (FB)
unnamed: C4.1, U12.13 (INTVCC)
unnamed: R42.1, U12.3 (RT)
unnamed: C6.2, U12.2 (TR/SS)
PAYLOAD_BATT_ENABLE: U9.24 (GPA3); also elsewhere on the board
PAYLOAD_PWR_ENABLE: U9.22 (GPA1); also elsewhere on the board
RF2_IO0: U9.27 (GPA6); also elsewhere on the board
RF2_IO1: U9.26 (GPA5); also elsewhere on the board
RF2_RX_EN: U9.25 (GPA4); also elsewhere on the board
RF2_TX_EN: U9.28 (GPA7); also elsewhere on the board
RF_VCC: C8.1, C12.1, L5.2, R63.2, TP5.1 (1_1), U12.14 (BIAS); also elsewhere on the board
SCL0: U8.5 (SCL), U9.12 (SCK), U16.5 (SCL); also elsewhere on the board
SDA0: U8.6 (SDA), U9.13 (SDA), U16.6 (SDA); also elsewhere on the board
VBUS: D15.2 (A); also elsewhere on the board
VBUSP: C1.1, C3.1, C19.1, C25.1, D15.1 (K), J20.2, J20.4, J30.1, R124.1, U10.13 (VIN), U10.14 (VCC), U12.4 (EN/UV), U12.5 (VIN), U12.6 (VIN); also elsewhere on the board
VSOLAR: J1.1, J1.2, J2.1, J2.2, J6.1, J6.2, J9.1, J9.2, J11.1, J11.2, J13.1, J13.2, R108.1, U8.1 (IN+)
~3v3_RESET: R124.2, U10.7 (EN); also elsewhere on the board
~CHARGE: IC6.4 (~CHRG), R70.2, U9.8 (GPB7)
~GPIO_EXPANDER_RESET: U9.18 (~RESET); also elsewhere on the board

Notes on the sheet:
I2C Address: 0x41
Regulator - 3.3V OUT
I2C Address: 0x40
Solar Power Monitor
Battery Power Monitor
VBATT 4.5 to 18V
VSOLAR 9V to 40V
2S Li-Ion Battery Solar Charging Circuit
Schottky Diode
Test Points
